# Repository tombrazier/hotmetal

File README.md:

# Hot Metal Brewbot

This project started as an Arduino PID controller for my coffee machine and gradually became a lot more. Read about it [here](http://tomblog.firstsolo.net/index.php/hobbies/pimping-my-coffee-machine/). See a video of the machine in action [here](https://www.youtube.com/watch?v=up54jM5fQOQ).

Presently there is just a controller PCB and firmware. In time I plan to build a front panel PCB as well. The board is designed to mount neatly in a Gaggia Baby machine but there is scope for other layouts for different machines. The circuit diagram would work with pretty much all machines with some modifications to the firmware.

`hardware/controller` contains EAGLE CAD files for the controller PCB which is an Arduino Nano shield.

`hardware/schematics` contains PDFs of the schematics for release versions of the controller. Saves hacing to have EAGLE installed and also gives past versions.

`firmware/controller` contains the Arduino source code.

`hardware/controller/DesignNotes.txt` contains a lot of useful information as well as notes about what needs doing next.

The present revision of my controller is 2.0, but I already know of some things I would like to change in 2.1. `DesignNotes.txt` documents these.

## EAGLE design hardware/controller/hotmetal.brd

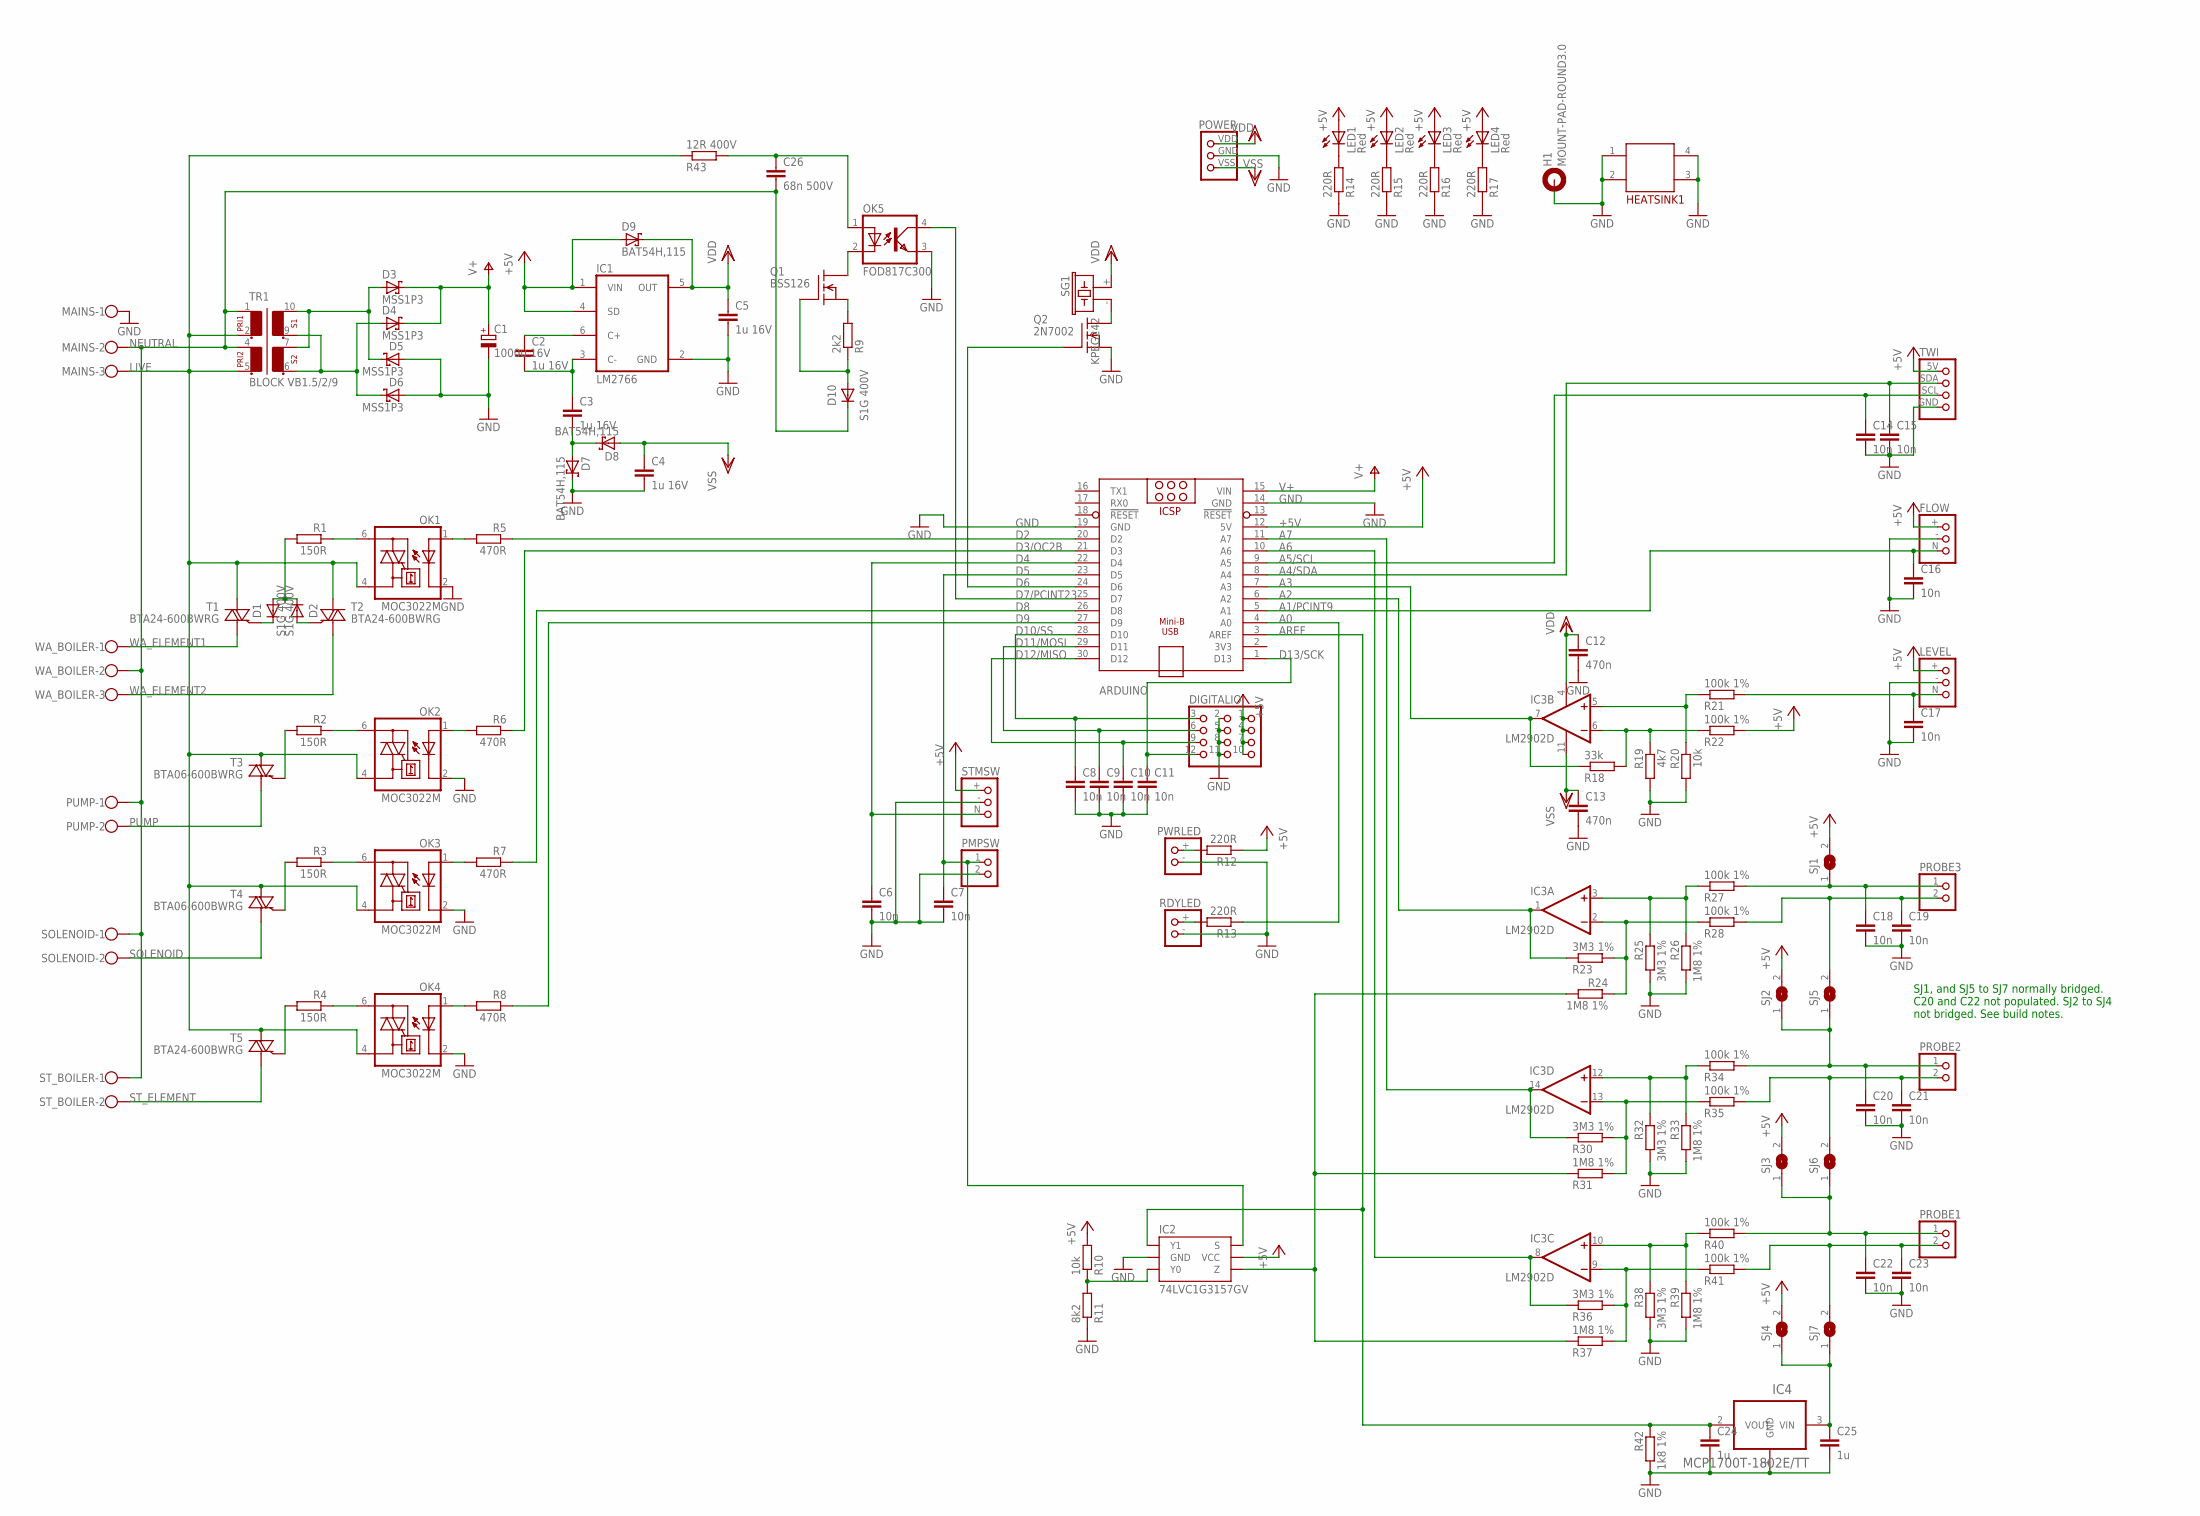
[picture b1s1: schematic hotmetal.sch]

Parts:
ARDUINO: ARDUINO_NANO
C1: 1000u 16V; E5-10,5
C2, C3, C4, C5: 1u 16V; C0603K
C6, C7, C8, C9, C10, C11, C14, C15, C16, C17, C18, C19, C20, C21, C22, C23: 10n; C0603K
C12, C13: 470n; C0603K
C24, C25: 1u; C0603K
C26: 68n 500V; C1210K
D1, D2, D10: S1G 400V; DO214AC
D3, D4, D5, D6: MSS1P3; POWERDI323
D7, D8, D9: BAT54H,115; SOD123F
DIGITALIO: HDR4X3PWR
FLOW: HDR3PWR
H1: MOUNT-PAD-ROUND3.0; 3,0-PAD
HEATSINK1: HOTMETALHEATSINK
IC1: LM2766; SOT23-6
IC2: 74LVC1G3157GV; SOT457
IC3: LM2902D; SO14
IC4: MCP1700T-1802E/TT; SOT23
LED1, LED2, LED3, LED4: Red; SML0805
LEVEL: HDR3PWR
MAINS: W237-103
OK1, OK2, OK3, OK4: MOC3022M; DIL06
OK5: FOD817C300; DIL04
PMPSW: HDR2
POWER: HDR3VDDVSS; HDR2VDDVSS
PROBE1, PROBE2, PROBE3: HDR2
PUMP: W237-102
PWRLED: HDR2PWR
Q1: BSS126; SOT23
Q2: 2N7002; SOT23
R1, R2, R3, R4: 150R; 0204/7
R5, R6, R7, R8: 470R; R0805
R9: 2k2; R0805
R10, R20: 10k; R0805
R11: 8k2; R0805
R12, R13, R14, R15, R16, R17: 220R; R0805
R18: 33k; R0805
R19: 4k7; R0805
R21, R22, R27, R28, R34, R35, R40, R41: 100k 1%; R0805
R23, R25, R30, R32, R36, R38: 3M3 1%; R0805
R24, R26, R31, R33, R37, R39: 1M8 1%; R0805
R42: 1k8 1%; R0805
R43: 12R 400V; R0805
RDYLED: HDR2PWR
SG1: KPEG242; F/CM12P
SJ1, SJ2, SJ3, SJ4, SJ5, SJ6, SJ7: SJ
SOLENOID: W237-102
STMSW: HDR3PWR
ST_BOILER: W237-102
T1, T2, T5: BTA24-600BWRG; TO220FACEDOWN
T3, T4: BTA06-600BWRG; TO220FACEDOWN
TR1: BLOCK VB1.5/2/9; T2P2S
TWI: HDR4TWI
WA_BOILER: W237-103

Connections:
+5V: ARDUINO.12 (5V), D9.A, DIGITALIO.1, DIGITALIO.4, DIGITALIO.7, DIGITALIO.10, FLOW.+ (1), IC1.1 (VIN), IC1.4 (SD), IC2.5 (VCC), LED1.A, LED2.A, LED3.A, LED4.A, LEVEL.+ (1), R10.2, R12.1, R22.2, SJ1.2, SJ2.2, SJ3.2, SJ4.2, STMSW.+ (1), TWI.5V (1)
A0: ARDUINO.4 (A0), R13.1
A1/PCINT9: ARDUINO.5 (A1), C16.1, FLOW.N (3)
A2: ARDUINO.6 (A2), IC3.1 (OUT), R23.1
A3: ARDUINO.7 (A3), IC3.7 (OUT), R18.1
A4/SDA: ARDUINO.8 (A4), C15.1, TWI.SDA (2)
A5/SCL: ARDUINO.9 (A5), C14.1, TWI.SCL (3)
A6: ARDUINO.10 (A6), IC3.8 (OUT), R36.1
A7: ARDUINO.11 (A7), IC3.14 (OUT), R30.1
AREF: ARDUINO.3 (AREF), C24.1, IC2.1 (Y1), IC4.2 (VOUT), R42.1
D2: ARDUINO.20 (D2), R5.1
D3/OC2B: ARDUINO.21 (D3), R6.1
D4: ARDUINO.22 (D4), C6.1, STMSW.N (3)
D5: ARDUINO.23 (D5), C7.1, IC2.6 (S), PMPSW.1
D6: ARDUINO.24 (D6), Q2.1 (G)
D7/PCINT23: ARDUINO.25 (D7), OK5.4 (COL)
D8: ARDUINO.26 (D8), R7.1
D9: ARDUINO.27 (D9), R8.1
D10/SS: ARDUINO.28 (D10), C8.1, DIGITALIO.3
D11/MOSI: ARDUINO.29 (D11), C9.1, DIGITALIO.6
D12/MISO: ARDUINO.30 (D12), C10.1, DIGITALIO.9
D13/SCK: ARDUINO.1 (D13), C11.1, DIGITALIO.12
GND: ARDUINO.14 (GND), ARDUINO.19 (GND), C1.-, C4.2, C5.2, C6.2, C7.2, C8.2, C9.2, C10.2, C11.2, C12.2, C13.2, C14.2, C15.2, C16.2, C17.2, C18.2, C19.2, C20.2, C21.2, C22.2, C23.2, C24.2, C25.2, D5.A, D6.A, D7.C, DIGITALIO.2, DIGITALIO.5, DIGITALIO.8, DIGITALIO.11, FLOW.- (2), H1.B3,0, HEATSINK1.1, HEATSINK1.2, HEATSINK1.3, HEATSINK1.4, IC1.2 (GND), IC2.2 (GND), IC4.1 (GND), LEVEL.- (2), MAINS.1, OK1.2 (C), OK2.2 (C), OK3.2 (C), OK4.2 (C), OK5.3 (EMIT), PMPSW.2, POWER.GND (2), PWRLED.- (2), Q2.2 (S), R11.1, R14.1, R15.1, R16.1, R17.1, R19.2, R20.2, R25.2, R26.2, R32.2, R33.2, R38.2, R39.2, R42.2, RDYLED.- (2), STMSW.- (2), TWI.GND (4)
LIVE: MAINS.3, OK1.4 (A1), OK2.4 (A1), OK3.4 (A1), OK4.4 (A1), R43.1, T1.T2 (A2), T2.T2 (A2), T3.T2 (A2), T4.T2 (A2), T5.T2 (A2), TR1.2, TR1.5
unnamed: OK3.1 (A), R7.2
unnamed: OK1.1 (A), R5.2
unnamed: OK4.1 (A), R8.2
unnamed: R3.2, T4.G
unnamed: OK3.6 (A2), R3.1
unnamed: D1.A, D2.C, R1.2
unnamed: R4.2, T5.G
unnamed: OK4.6 (A2), R4.1
unnamed: OK1.6 (A2), R1.1
unnamed: C21.1, PROBE2.2, R35.2, SJ6.2
unnamed: C22.1, PROBE1.1, R40.2, SJ3.1, SJ6.1
unnamed: C20.1, PROBE2.1, R34.2, SJ2.1, SJ5.1
unnamed: IC3.3 (+IN), R25.1, R26.1, R27.1
unnamed: D1.C, T1.G
unnamed: D2.A, T2.G
unnamed: C17.1, LEVEL.N (3), R21.2
unnamed: IC3.10 (+IN), R38.1, R39.1, R40.1
unnamed: IC3.9 (-IN), R36.2, R37.2, R41.1
unnamed: Q2.3 (D), SG1.- (2)
unnamed: LED3.C, R16.2
unnamed: C2.1, IC1.6 (C+)
unnamed: OK2.1 (A), R6.2
unnamed: R2.2, T3.G
unnamed: OK2.6 (A2), R2.1
unnamed: PWRLED.+ (1), R12.2
unnamed: R13.2, RDYLED.+ (1)
unnamed: C2.2, C3.1, IC1.3 (C-)
unnamed: C23.1, PROBE1.2, R41.2, SJ7.2
unnamed: C26.1, OK5.1 (A), R43.2
unnamed: D10.A, Q1.1 (G), R9.1
unnamed: C19.1, PROBE3.2, R28.2, SJ5.2
unnamed: C18.1, PROBE3.1, R27.2, SJ1.1
unnamed: IC3.12 (+IN), R32.1, R33.1, R34.1
unnamed: IC3.2 (-IN), R23.2, R24.1, R28.1
unnamed: IC3.13 (-IN), R30.2, R31.2, R35.1
unnamed: IC3.5 (+IN), R20.1, R21.1
unnamed: IC2.3 (Y0), R10.1, R11.2
unnamed: IC2.4 (Z), R24.2, R31.1, R37.1
unnamed: D3.A, D5.C, TR1.7, TR1.10
unnamed: IC3.6 (-IN), R18.2, R19.1, R22.1
unnamed: C25.1, IC4.3 (VIN), SJ4.1, SJ7.1
unnamed: LED1.C, R14.2
unnamed: LED2.C, R15.2
unnamed: LED4.C, R17.2
unnamed: D4.A, D6.C, TR1.6, TR1.9
unnamed: Q1.2 (S), R9.2
unnamed: OK5.2 (C), Q1.3 (D)
unnamed: C3.2, D7.A, D8.C
NEUTRAL: C26.2, D10.C, MAINS.2, PUMP.1, SOLENOID.1, ST_BOILER.1, TR1.1, TR1.4, WA_BOILER.2
PUMP: PUMP.2, T3.T1 (A1)
SOLENOID: SOLENOID.2, T4.T1 (A1)
ST_ELEMENT: ST_BOILER.2, T5.T1 (A1)
V+: ARDUINO.15 (VIN), C1.+, D3.C, D4.C
VDD: C5.1, C12.1, D9.C, IC1.5 (OUT), IC3.4 (V+), POWER.VDD (1), SG1.+ (1)
VSS: C4.1, C13.1, D8.A, IC3.11 (V-), POWER.VSS (3)
WA_ELEMENT1: T1.T1 (A1), WA_BOILER.1
WA_ELEMENT2: T2.T1 (A1), WA_BOILER.3

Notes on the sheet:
SJ1, and SJ5 to SJ7 normally bridged. C20 and C22 not populated. SJ2 to SJ4 not bridged. See build notes.

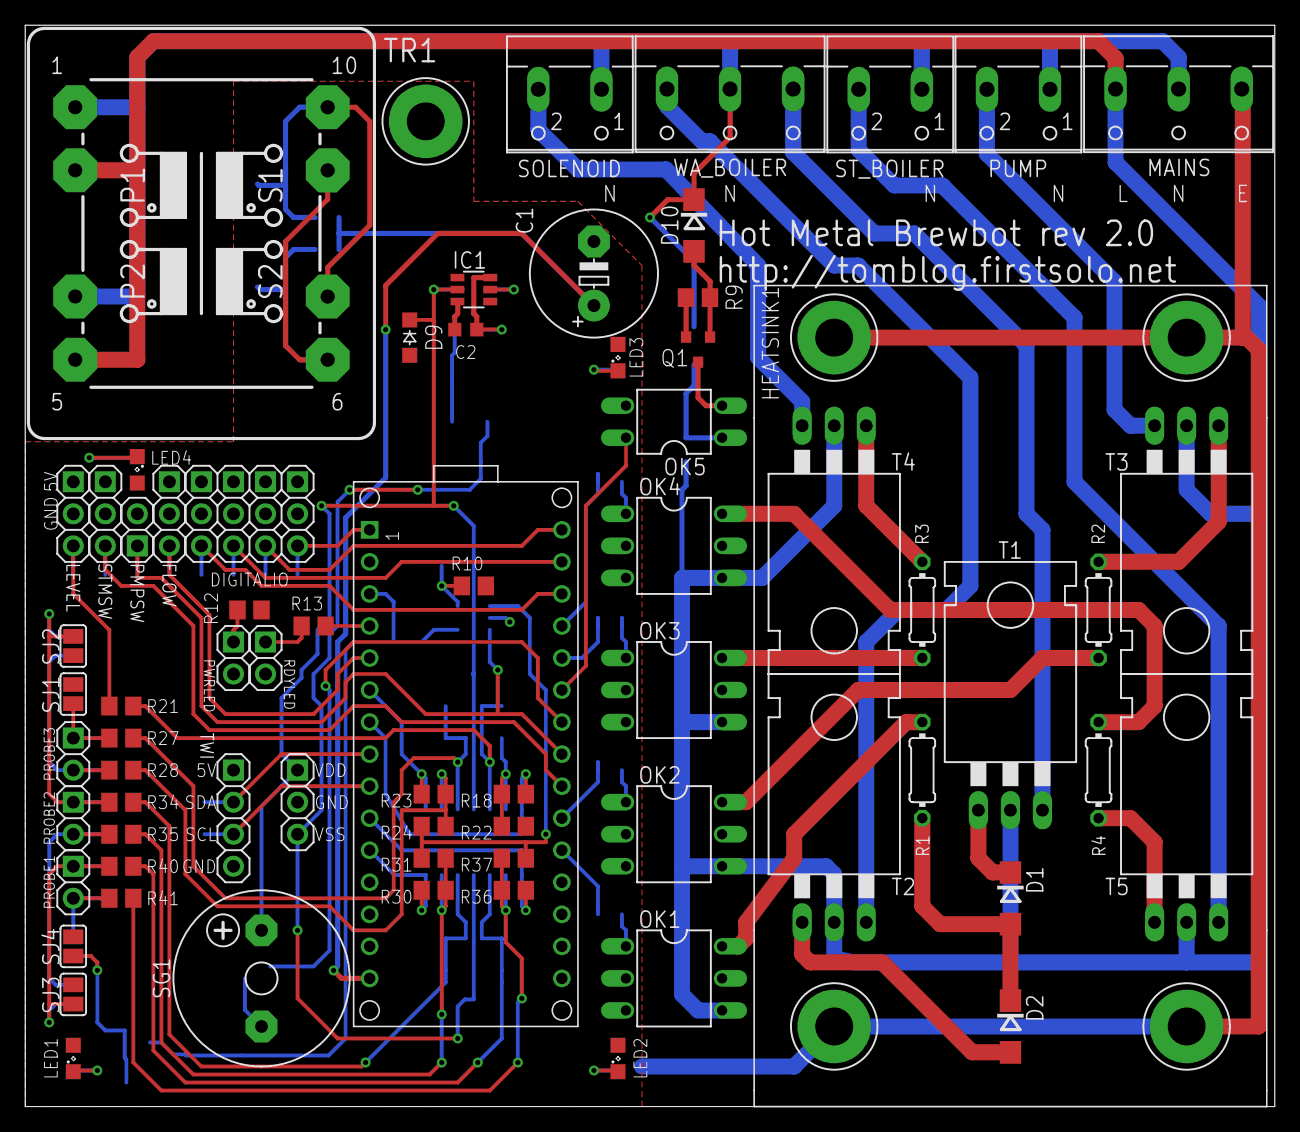
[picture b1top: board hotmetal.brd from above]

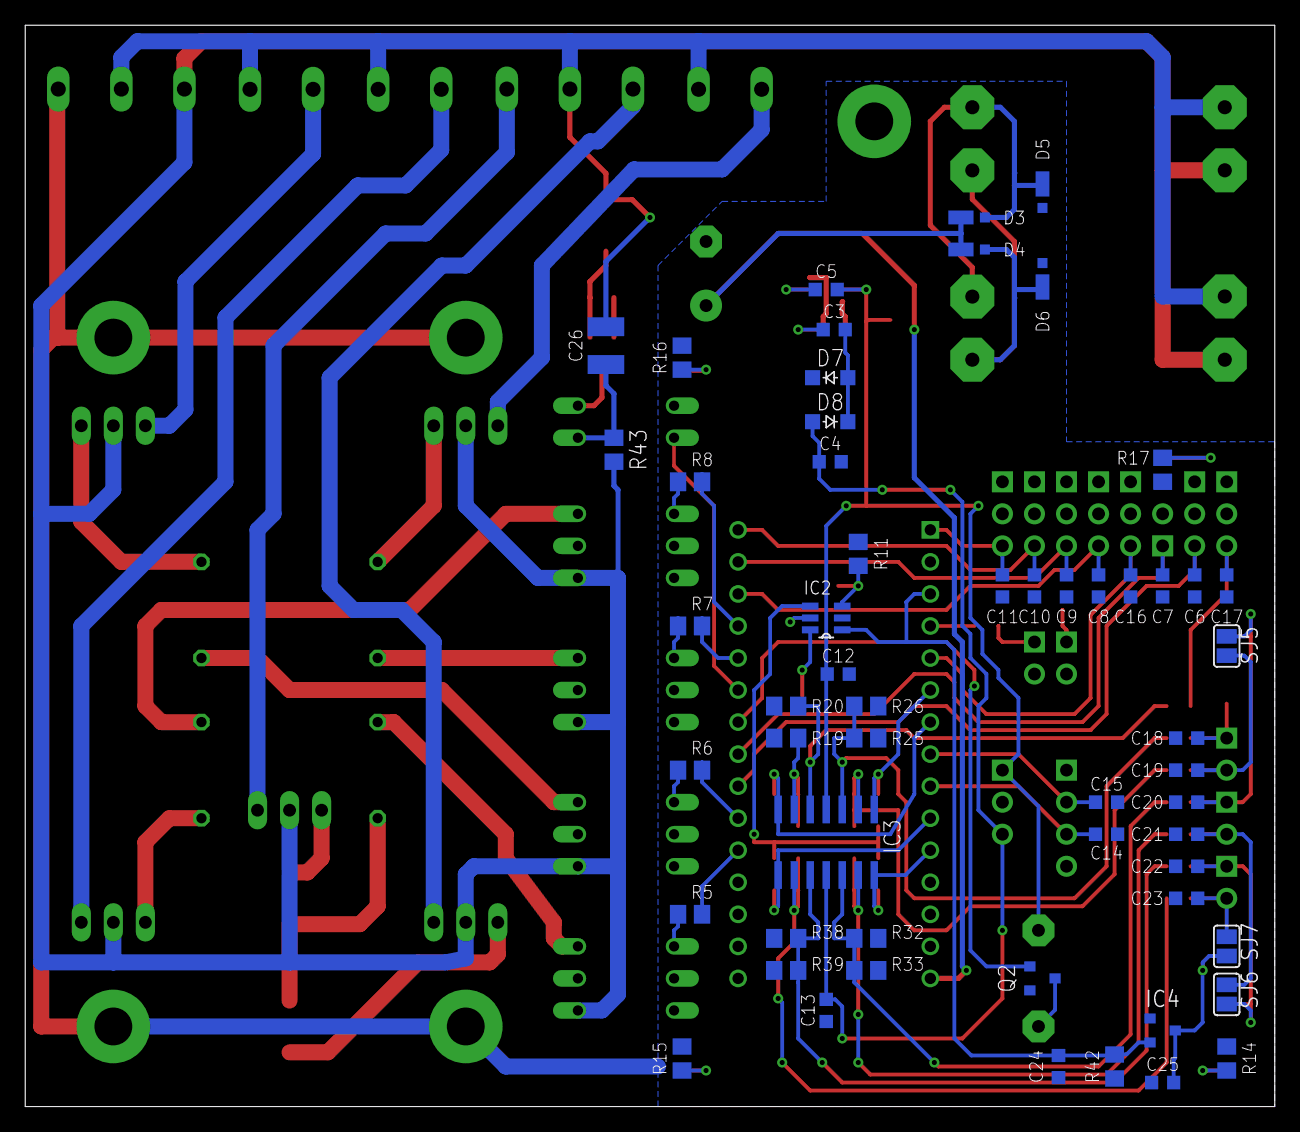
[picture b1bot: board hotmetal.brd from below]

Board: 2 copper layers, 99.1 x 85.7 mm, 127 parts (56 on the bottom side), 81 nets.

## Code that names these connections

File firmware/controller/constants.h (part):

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// operating parameters
static const double BREW_SETPOINT = 97.0;       // °C
static const double STEAM_SETPOINT = 166.0;     // °C average boiler temperature (bearing in mind element sides are a hotter and other sides cooler)
static const double MAX_FLOW_RATE = 10.0;       // ml/s well over what the pump can produce just to be sure
static const double BREW_FLOW_RATE_2CUP = 3.5;  // ml/s
static const double BREW_FLOW_RATE_1CUP = 2.5;  // ml/s half of BREW_FLOW_RATE_2CUP would be good, but it's a little close to the flow meter's min rate
static const double MIN_FLOW_RATE = 2.0;        // ml/s where the flow rate begins to be able to be controlled
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static const double BREW_VOLUME_1CUP = 60.0;    // ml
static const double MIN_RESERVOIR_VOLUME = 100.0;// ml
static const unsigned INACTIVITY_TIMEOUT = 1200;// seconds with no activity before stopping heating activating the buzzer (20 minutes)
static const unsigned long BACKFLUSH_STALL_TIME = 1000000l; // microseconds to wait for while pump is stalled before flushing
static const unsigned long BACKFLUSH_FLUSH_TIME = 2500000l; // microseconds to wait for while pump is flushing before restarting
static const double STEAM_PUMP_PULSE_TEMP = 140.0;// temperature at which pulsing the pump begins in steam mode.
static const double STEAM_PUMP_PULSE_DUTY = 0.12;// duty cycle for pulsing the pump in steam mode.

// physical charcteristics of the AVR's internal temperature probe and circuitry
static const double PCBTEMP_OFFSET = 352.0;               // °C the offset to subtract to get the PCB's temperature once the AVR's self-heating is complete
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static const double BETA3 = 3950.0;                         // the beta value of the NTC probe

// characterisitics of the flow meter
static const double FLOW_METER_DEBOUNCE_TIME = 0.02; // any state change within 20ms of the last is considered a bounce error (from pump vibration)

// characteristics of the level meter probe
static const long LEVEL_PROBE_FULL_VALUE = 905;  // ADC reading when reservoir full (approximate - very dependent on weather)
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static const double TRIAC_MAX_TEMPERATURE = 115.0;              // °C max junction temperature from datasheet minus 10°C safety margin

// pin mappings
static const uint8_t SOLENOID_PIN = 8;         //
static const uint8_t PUMP_POWER_PIN = 3;       // = OC2B
static const uint8_t BOILER_POWER_PIN = 2;     //
static const uint8_t ST_BOILER_POWER_PIN = 9;  //
static const uint8_t STEAM_SW_PIN = 4;         //
static const uint8_t PUMP_SW_PIN = 10;         // = SS (needed for SPI slave)
static const uint8_t TEMP_OKAY_LED_PIN = 14;   // = PC0
static const uint8_t FLOW_METER_PIN = 15;      // = PC1 = PCINT9
#define FLOW_METER_PCINT PCINT9
static const uint8_t MAINS_POLARITY_PIN = 7;   // = PCINT23
#define MAINS_POLARITY_PCINT PCINT23
static const uint8_t PIEZO_BUZZER_PIN = 6;     //
static const uint8_t TEMP_LOW_RANGE_PIN = 5;   //
static const uint8_t TEMP_PROBE_1_ADCPIN = 6;  //
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
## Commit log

2021-07-28 initializing repository with rev 2.0 plus some modifications
2021-07-29 Added schematic PDFs of PCB releases for quick reference
2021-07-29 Exported the PDF the right way round!
2021-09-22 Removed brand specific comment
2021-09-22 Implemented flow meter calibration and recalibrated flow meter (getting quite a different curve)
2021-09-22 Faster serial comms
2021-09-22 Also track flow meter pulses in serial output

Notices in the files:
firmware/controller/constants.h:
Copyright (C) 2010-2020 Tom Brazier (http://tomblog.firstsolo.net)
modify it under the terms of the GNU General Public License as
published by the Free Software Foundation, either version 3 of the
License, or (at your option) any later version.
